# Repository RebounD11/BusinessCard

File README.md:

# Overview

This is a simple 4-layer PCB, the size of a credit card (approximately - 85.6 mm x 54 mm with rounded corners) that has the main purpose of being a business card and secondary purposes of not beoming e-waste once the novelty has worn off.  

# Functionality

## First impression 

When handing out the card, the front side will look like this:

## Power up

## Connecting

## Clearing connections

## Clock functionality

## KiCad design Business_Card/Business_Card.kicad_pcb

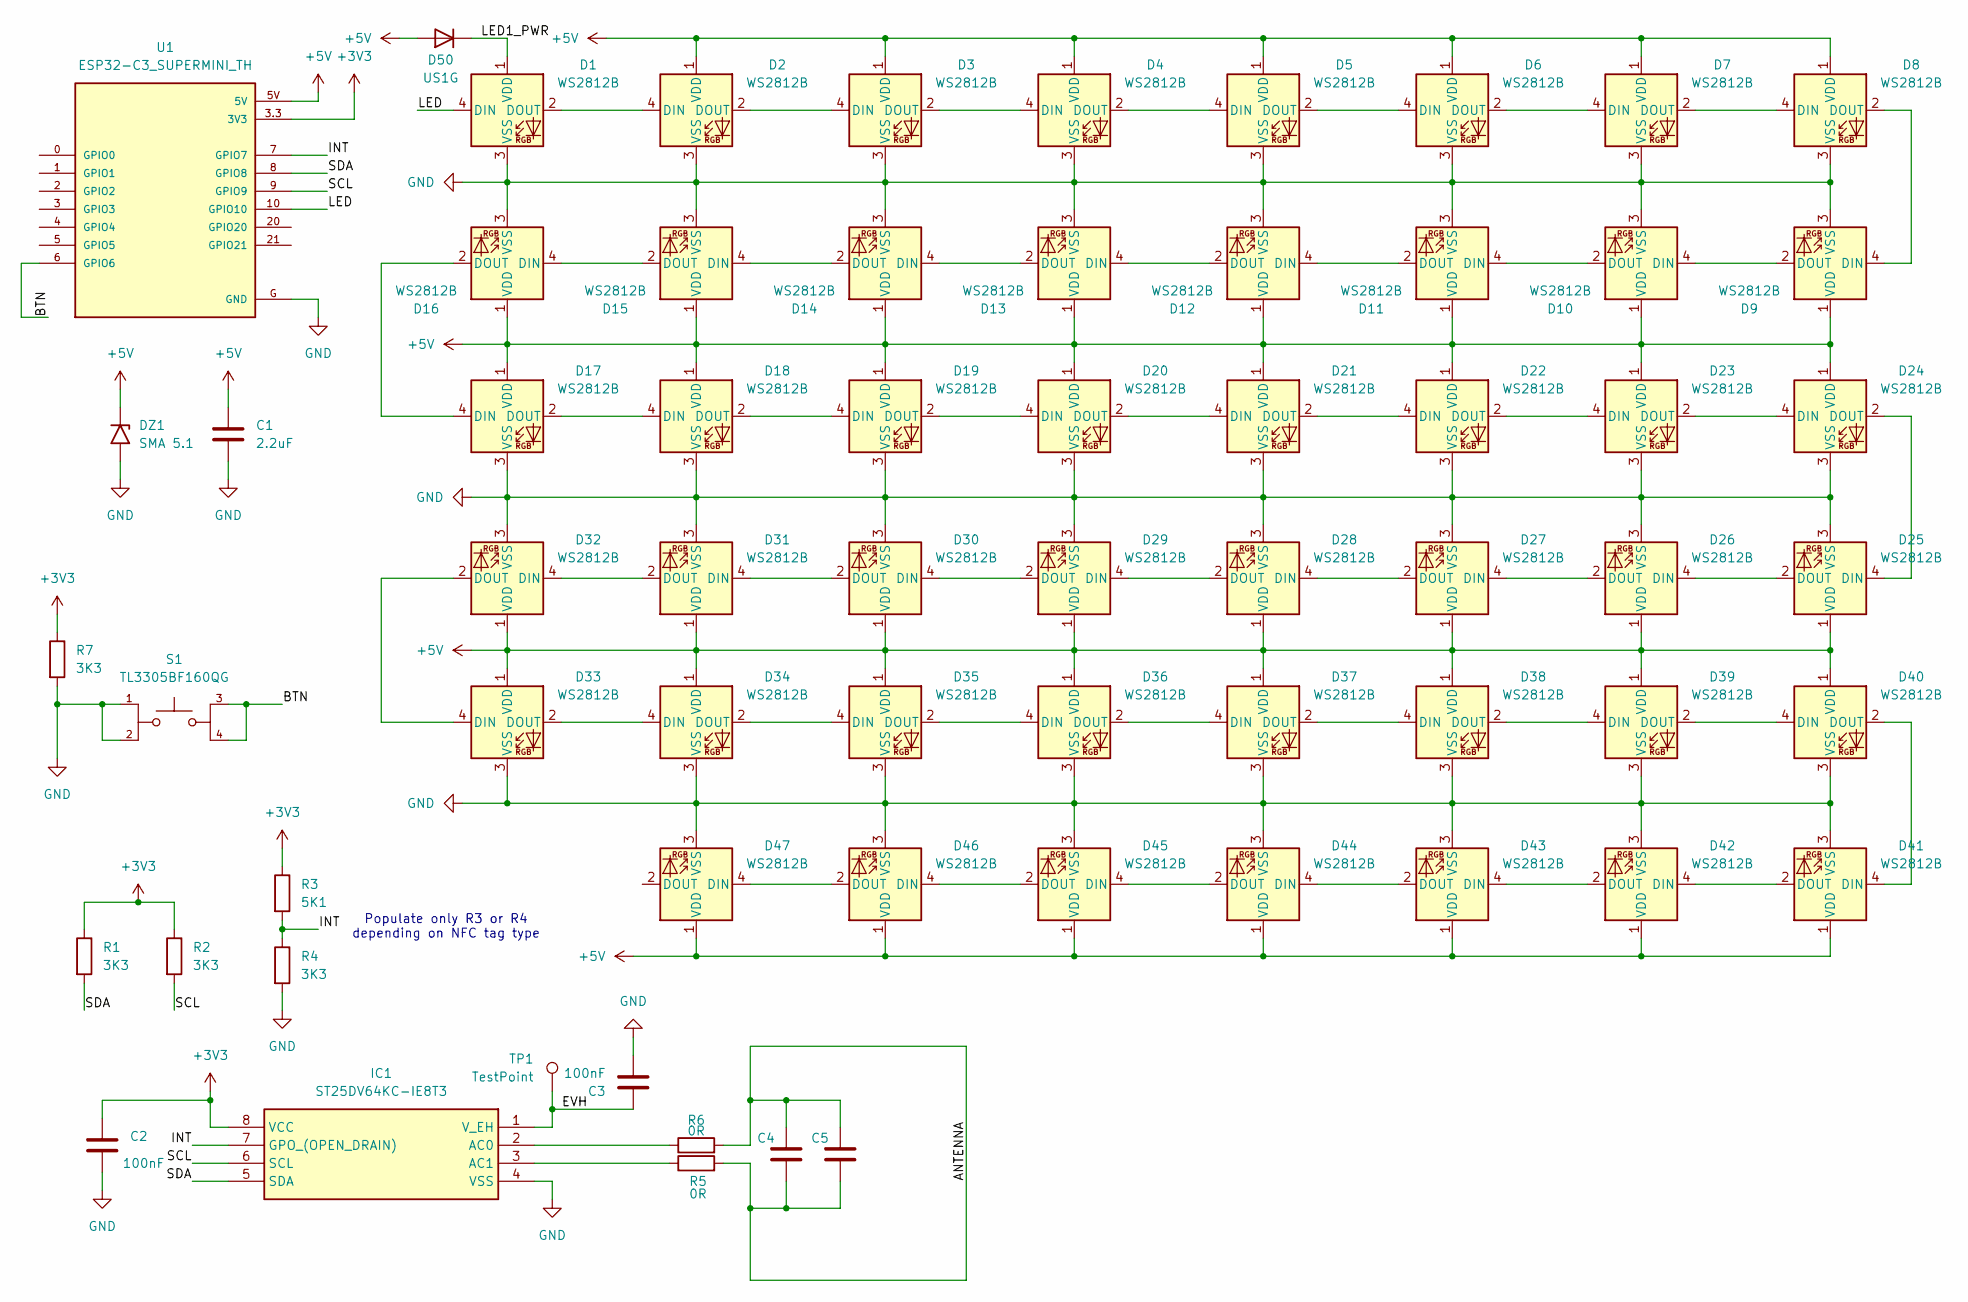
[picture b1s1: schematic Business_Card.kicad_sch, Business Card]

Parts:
C1: 2.2uF; C_0805_2012Metric_Pad1.18x1.45mm_HandSolder
C2, C3: 100nF; C_0805_2012Metric_Pad1.18x1.45mm_HandSolder
C4, C5: C_0402_1005Metric_Pad0.74x0.62mm_HandSolder
D1, D2, D3, D4, D5, D6, D7, D8, D9, D10, D11, D12, D13, D14, D15, D16, D17, D18, D19, D20, D21, D22, D23, D24, D25, D26, D27, D28, D29, D30, D31, D32, D33, D34, D35, D36, D37, D38, D39, D40, D41, D42, D43, D44, D45, D46, D47: WS2812B; LED_WS2812B-Mini_PLCC4_3.5x3.5mm
D50: US1G; D_SMA_Handsoldering
DZ1: SMA 5.1; D_SMA_Handsoldering
IC1: ST25DV64KC-IE8T3; SOP65P640X120-8N; Mouser Part Number 511-ST25DV64KC-IE8T3
R1, R2, R4, R7: 3K3; R_0805_2012Metric_Pad1.20x1.40mm_HandSolder
R3: 5K1; R_0805_2012Metric_Pad1.20x1.40mm_HandSolder
R5, R6: 0R; R_0402_1005Metric_Pad0.72x0.64mm_HandSolder
S1: TL3305BF160QG; SW_TL3305BF160QG; PARTREV C
TP1: TestPoint; TestPoint_Pad_D1.0mm
U1: ESP32-C3_SUPERMINI_TH; MODULE_ESP32-C3_SUPERMINI_TH

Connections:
+3V3: C2.1, IC1.8 (VCC), R1.1, R2.1, R3.1, R7.1, U1.3.3 (3V3)
+5V: C1.1, D2.1 (VDD), D3.1 (VDD), D4.1 (VDD), D5.1 (VDD), D6.1 (VDD), D7.1 (VDD), D8.1 (VDD), D9.1 (VDD), D10.1 (VDD), D11.1 (VDD), D12.1 (VDD), D13.1 (VDD), D14.1 (VDD), D15.1 (VDD), D16.1 (VDD), D17.1 (VDD), D18.1 (VDD), D19.1 (VDD), D20.1 (VDD), D21.1 (VDD), D22.1 (VDD), D23.1 (VDD), D24.1 (VDD), D25.1 (VDD), D26.1 (VDD), D27.1 (VDD), D28.1 (VDD), D29.1 (VDD), D30.1 (VDD), D31.1 (VDD), D32.1 (VDD), D33.1 (VDD), D34.1 (VDD), D35.1 (VDD), D36.1 (VDD), D37.1 (VDD), D38.1 (VDD), D39.1 (VDD), D40.1 (VDD), D41.1 (VDD), D42.1 (VDD), D43.1 (VDD), D44.1 (VDD), D45.1 (VDD), D46.1 (VDD), D47.1 (VDD), D50.2 (A), DZ1.1 (A1), U1.5V
/ANTENNA: C4.1, C4.2, C5.1, C5.2, R5.2, R6.2
/BTN: S1.3, S1.4, U1.6 (GPIO6)
/EVH: C3.1, IC1.1 (V_EH), TP1.1
/INT: IC1.7 (GPO_(OPEN_DRAIN)), R3.2, R4.1, U1.7 (GPIO7)
/LED: D1.4 (DIN), U1.10 (GPIO10)
/LED1_PWR: D1.1 (VDD), D50.1 (K)
/SCL: IC1.6 (SCL), R2.2, U1.9 (GPIO9)
/SDA: IC1.5 (SDA), R1.2, U1.8 (GPIO8)
GND: C1.2, C2.2, C3.2, D1.3 (VSS), D2.3 (VSS), D3.3 (VSS), D4.3 (VSS), D5.3 (VSS), D6.3 (VSS), D7.3 (VSS), D8.3 (VSS), D9.3 (VSS), D10.3 (VSS), D11.3 (VSS), D12.3 (VSS), D13.3 (VSS), D14.3 (VSS), D15.3 (VSS), D16.3 (VSS), D17.3 (VSS), D18.3 (VSS), D19.3 (VSS), D20.3 (VSS), D21.3 (VSS), D22.3 (VSS), D23.3 (VSS), D24.3 (VSS), D25.3 (VSS), D26.3 (VSS), D27.3 (VSS), D28.3 (VSS), D29.3 (VSS), D30.3 (VSS), D31.3 (VSS), D32.3 (VSS), D33.3 (VSS), D34.3 (VSS), D35.3 (VSS), D36.3 (VSS), D37.3 (VSS), D38.3 (VSS), D39.3 (VSS), D40.3 (VSS), D41.3 (VSS), D42.3 (VSS), D43.3 (VSS), D44.3 (VSS), D45.3 (VSS), D46.3 (VSS), D47.3 (VSS), DZ1.2 (A2), IC1.4 (VSS), R4.2, R7.2, S1.1, S1.2, U1.G (GND)
unnamed: D1.2 (DOUT), D2.4 (DIN)
unnamed: D2.2 (DOUT), D3.4 (DIN)
unnamed: D3.2 (DOUT), D4.4 (DIN)
unnamed: D4.2 (DOUT), D5.4 (DIN)
unnamed: D5.2 (DOUT), D6.4 (DIN)
unnamed: D6.2 (DOUT), D7.4 (DIN)
unnamed: D7.2 (DOUT), D8.4 (DIN)
unnamed: D8.2 (DOUT), D9.4 (DIN)
unnamed: D9.2 (DOUT), D10.4 (DIN)
unnamed: D10.2 (DOUT), D11.4 (DIN)
unnamed: D11.2 (DOUT), D12.4 (DIN)
unnamed: D12.2 (DOUT), D13.4 (DIN)
unnamed: D13.2 (DOUT), D14.4 (DIN)
unnamed: D14.2 (DOUT), D15.4 (DIN)
unnamed: D15.2 (DOUT), D16.4 (DIN)
unnamed: D16.2 (DOUT), D17.4 (DIN)
unnamed: D17.2 (DOUT), D18.4 (DIN)
unnamed: D18.2 (DOUT), D19.4 (DIN)
unnamed: D19.2 (DOUT), D20.4 (DIN)
unnamed: D20.2 (DOUT), D21.4 (DIN)
unnamed: D21.2 (DOUT), D22.4 (DIN)
unnamed: D22.2 (DOUT), D23.4 (DIN)
unnamed: D23.2 (DOUT), D24.4 (DIN)
unnamed: D24.2 (DOUT), D25.4 (DIN)
unnamed: D25.2 (DOUT), D26.4 (DIN)
unnamed: D26.2 (DOUT), D27.4 (DIN)
unnamed: D27.2 (DOUT), D28.4 (DIN)
unnamed: D28.2 (DOUT), D29.4 (DIN)
unnamed: D29.2 (DOUT), D30.4 (DIN)
unnamed: D30.2 (DOUT), D31.4 (DIN)
unnamed: D31.2 (DOUT), D32.4 (DIN)
unnamed: D32.2 (DOUT), D33.4 (DIN)
unnamed: D33.2 (DOUT), D34.4 (DIN)
unnamed: D34.2 (DOUT), D35.4 (DIN)
unnamed: D35.2 (DOUT), D36.4 (DIN)
unnamed: D36.2 (DOUT), D37.4 (DIN)
unnamed: D37.2 (DOUT), D38.4 (DIN)
unnamed: D38.2 (DOUT), D39.4 (DIN)
unnamed: D39.2 (DOUT), D40.4 (DIN)
unnamed: D40.2 (DOUT), D41.4 (DIN)
unnamed: D41.2 (DOUT), D42.4 (DIN)
unnamed: D42.2 (DOUT), D43.4 (DIN)
unnamed: D43.2 (DOUT), D44.4 (DIN)
unnamed: D44.2 (DOUT), D45.4 (DIN)
unnamed: D45.2 (DOUT), D46.4 (DIN)
unnamed: D46.2 (DOUT), D47.4 (DIN)
unnamed: IC1.2 (AC0), R6.1
unnamed: IC1.3 (AC1), R5.1

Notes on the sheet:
Populate only R3 or R4 depending on NFC tag type

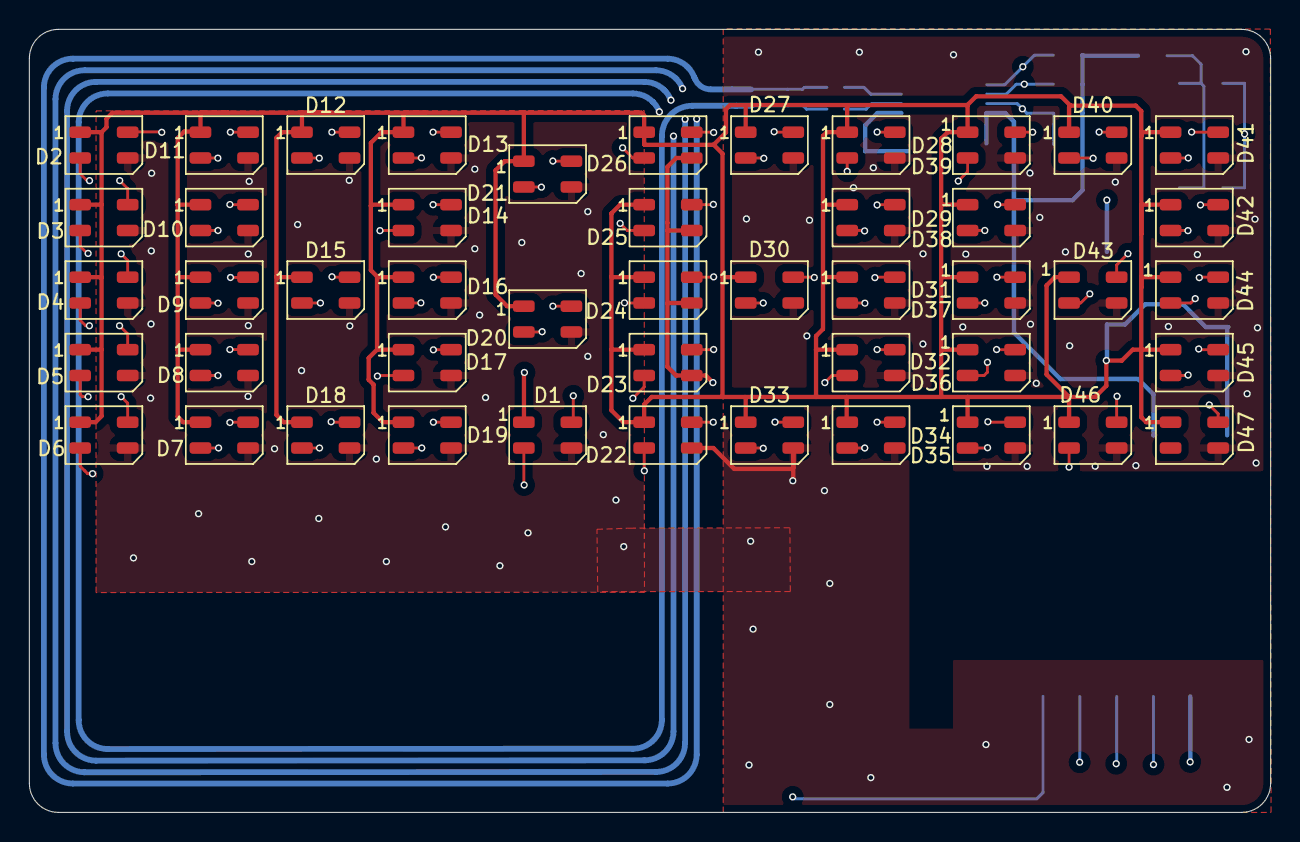
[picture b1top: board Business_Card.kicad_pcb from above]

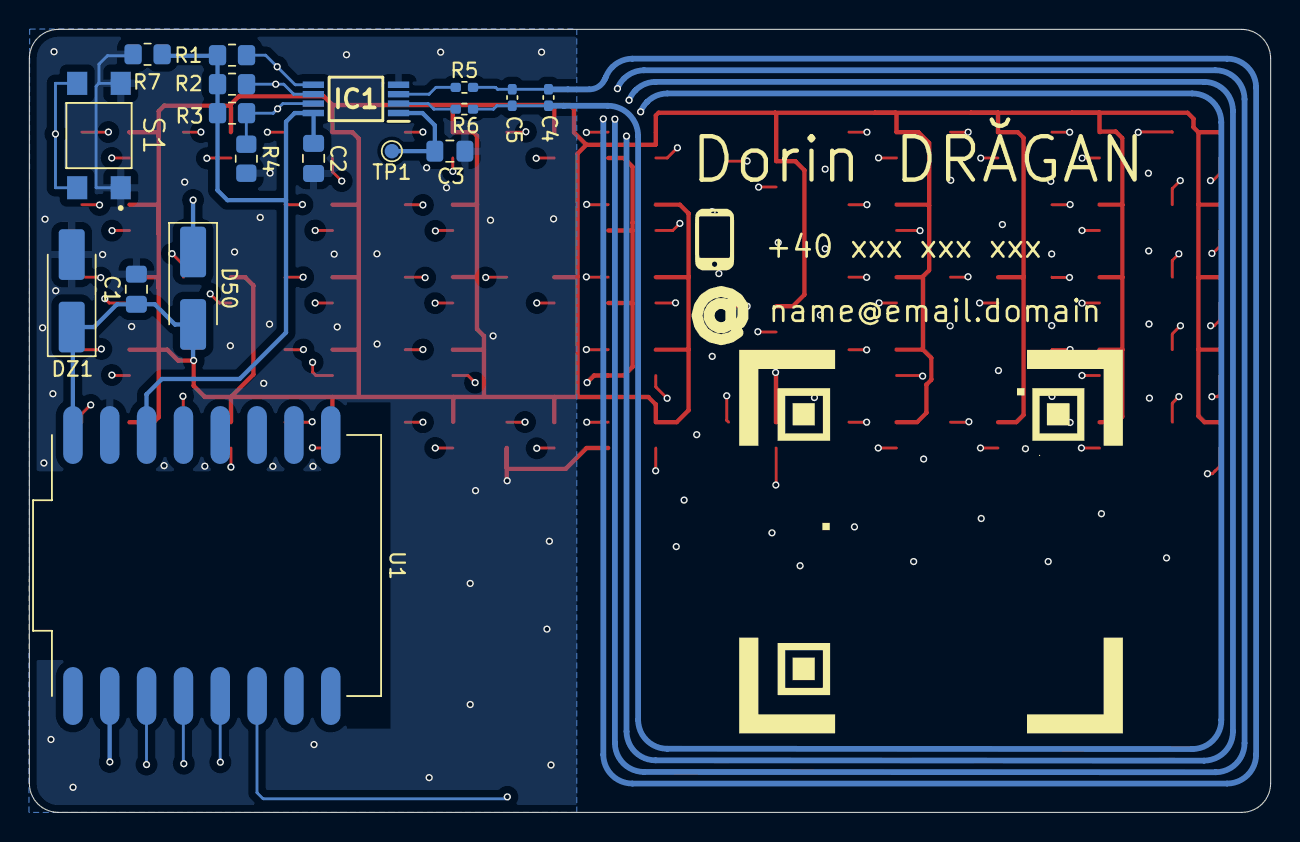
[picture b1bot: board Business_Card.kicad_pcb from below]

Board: 4 copper layers, 85.6 x 54.0 mm, 65 parts (18 on the bottom side), 59 nets.

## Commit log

2025-11-23 Arduin Sketch
    Bad code of functionality
2025-11-23 Delete Business_Card directory
    Typo
2025-11-23 Arduino Sketch
    Bad Arduino code to use with ESP32-C3 SuperMini
2025-11-23 Update Business_Card.ino
    Refresh implemented.
2025-11-23 KiCAD files
    Project, Schematic, Layout, Step, Gerbers
2025-11-23 Code outside KiCAD folder
    Moved outside of folder
2025-11-23 Delete Business_Card/Business_Card.ino
    Duplicate
2025-11-23 Delete Business_Card/Business_Card.kicad_pro
    Wrong version
2025-11-23 Delete Business_Card/Business_Card.kicad_sch
    Wrong version
2025-11-23 Correct versions
    Added measurements for NFC antenna
2025-11-23 Create Images folder
    Folder for images in the Readme
2025-11-23 Delete Images
    Not OK
2025-11-23 Create Readme_Images
    Create Images folder
2025-11-23 Upload Front view
    First view
2025-11-23 Create README.md
    Work in progress
2025-11-23 More useful images
    Images of the PCB
